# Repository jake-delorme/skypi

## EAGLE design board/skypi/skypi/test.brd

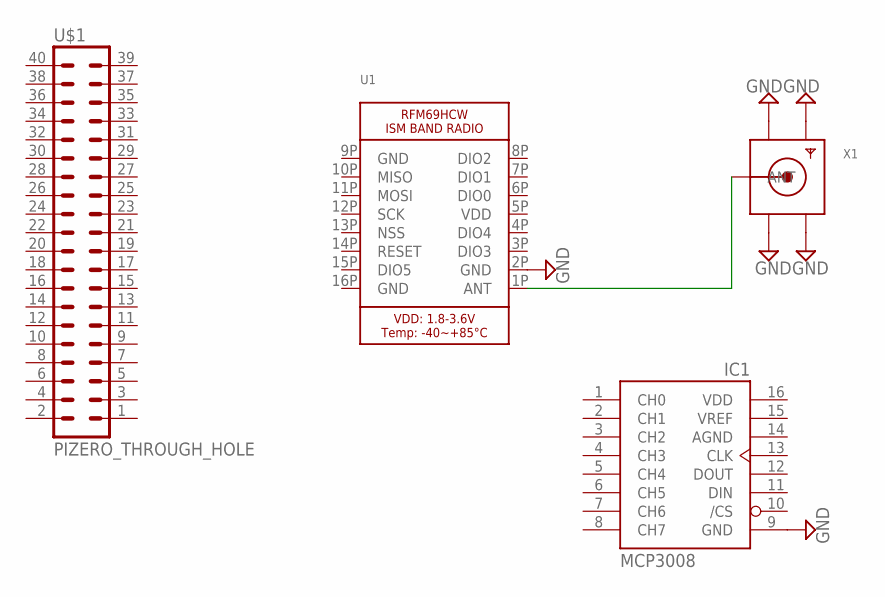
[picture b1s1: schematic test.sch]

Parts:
IC1: MCP3008; DIL16
U1: MICROBUILDER_RFM69HCW_SMT; MICROBUILDER_RFMHCW_SMT
U$1: PIZERO_THROUGH_HOLE; PIZERO_THOUGH_HOLE
X1: MICROBUILDER_SMACONNECTOR_EDGE; MICROBUILDER_SMA_EDGELAUNCH

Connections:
AGND: IC1.14 (AGND)
GND: IC1.9 (GND), U1.2P (GND), U1.9P (GND), U1.16P (GND), X1.GND@1 (GND4), X1.GND@2 (GND3), X1.GND@3 (GND2), X1.GND@4 (GND1)
unnamed: U1.1P (ANT), X1.P (ANT)
VDD: IC1.16 (VDD), U1.5P (VDD)

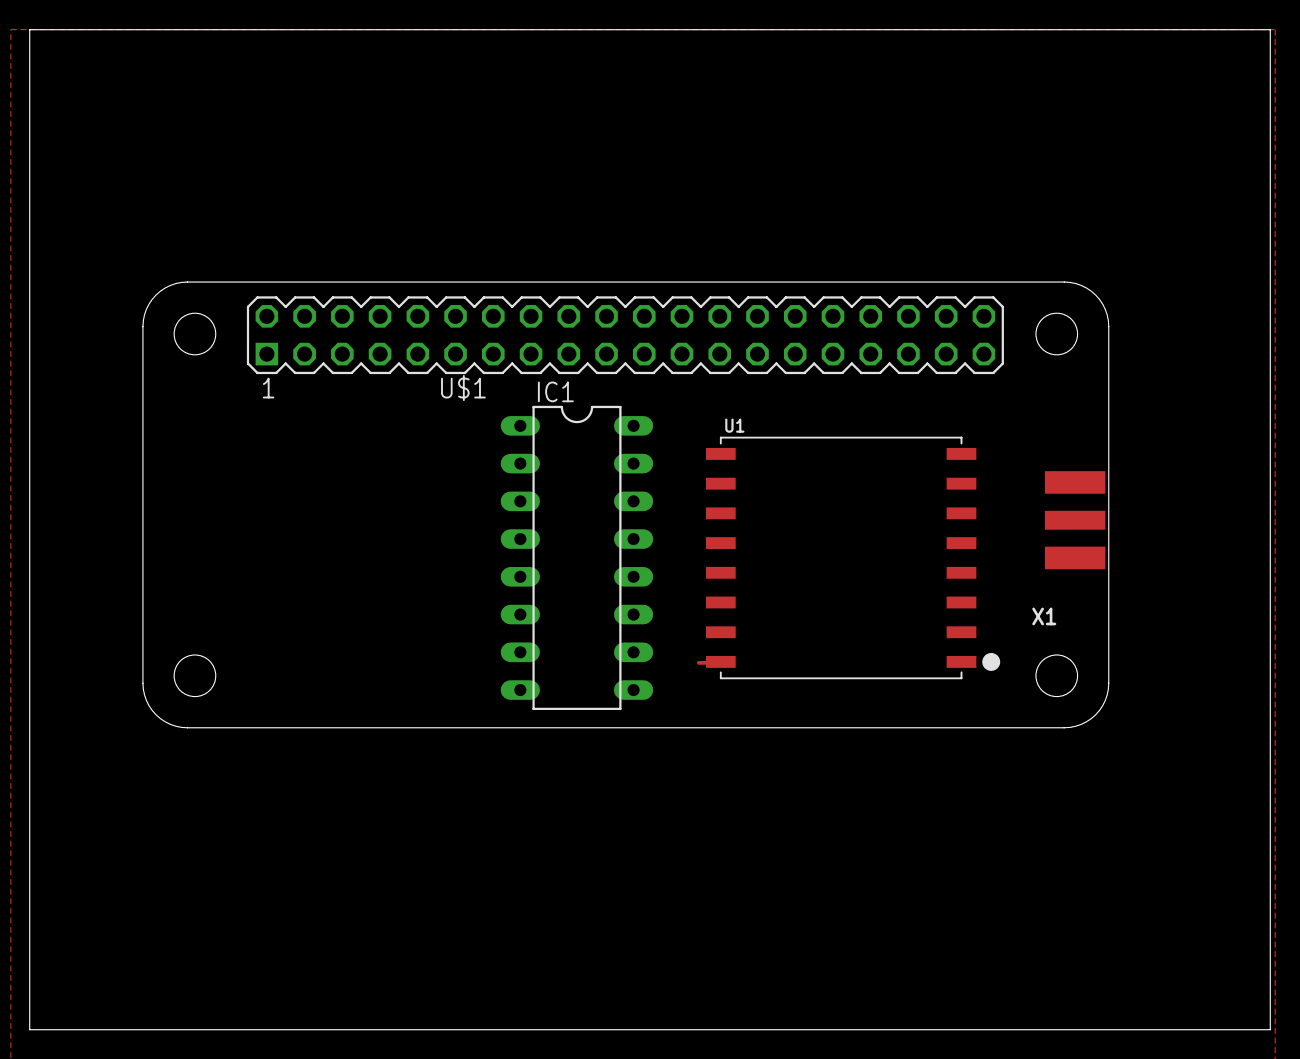
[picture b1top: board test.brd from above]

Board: 2 copper layers, 83.5 x 67.3 mm, 4 parts (0 on the bottom side), 3 nets.

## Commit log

2017-03-19 Cleanup
2017-03-19 blah
2017-03-20 stuff
2017-03-20 more blah
2017-03-21 gitignore .pyc
2017-03-21 Thread starter on all modules
2017-03-21 Queues
2017-03-22 stab at requirements
2017-03-25 setting up queing and message registration
2017-03-25 gps testing
2017-03-26 battery testing
2017-03-26 pylint gave me a 0.65/10 rating. fck you pylint
2017-04-09 sms testing
2017-04-09 removed unneeded pynema library
2017-04-18 playing with eagle
